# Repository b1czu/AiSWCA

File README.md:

# AiSWCA
AiSWCA is Steering Wheel Control Adapter

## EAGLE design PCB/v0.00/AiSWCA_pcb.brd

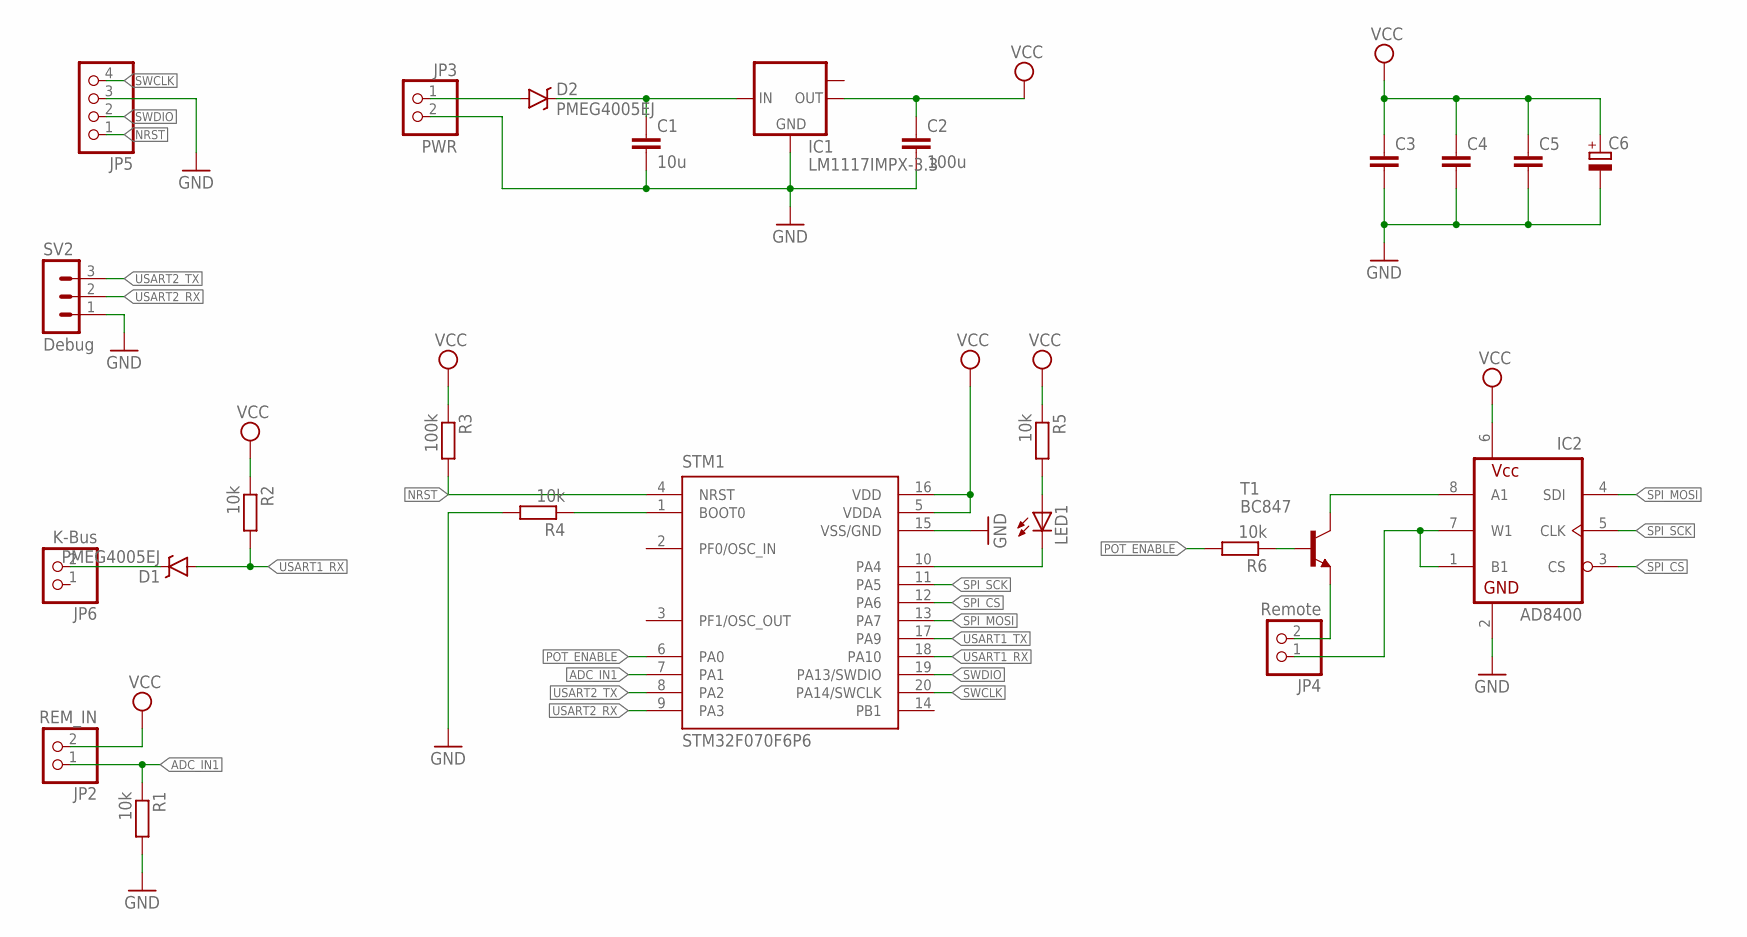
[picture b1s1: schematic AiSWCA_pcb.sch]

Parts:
C1: 10u; C0805
C2: 100u; C0805
C3, C4, C5: C-EUC0805; C0805
C6: CPOL-EUB/3528-21W; B/3528-21W
D1, D2: PMEG4005EJ; SOD-323
IC1: LM1117IMPX-3.3; SOT223
IC2: AD8400R; SO8
JP2: REM_IN; 1X02/90
JP3: PWR; 1X02/90
JP4: Remote; 1X02/90
JP5: PINHD-1X4/90; 1X04/90
JP6: K-Bus; 1X02/90
LED1: LEDCHIP-LED0805; CHIP-LED0805
R1, R2, R4, R5, R6: 10k; R0805
R3: 100k; R0805
STM1: STM32F070F6P6; TSSOP20
SV2: Debug; MA03-1
T1: BC847; SOT23

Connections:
ADC_IN1: JP2.1, R1.1, STM1.7 (PA1)
GND: C1.2, C2.2, C3.2, C4.2, C5.2, C6.-, IC1.1 (GND), IC2.2 (GND), JP3.2, JP5.3, R1.2, R4.2, STM1.15 (VSS/GND), SV2.1
unnamed: C1.1, D2.C, IC1.3 (IN)
unnamed: R4.1, STM1.1 (BOOT0)
unnamed: D1.C, JP6.2
unnamed: D2.A, JP3.1
unnamed: LED1.C, STM1.10 (PA4)
unnamed: LED1.A, R5.2
unnamed: JP4.2, T1.2 (E)
unnamed: IC2.8 (A1), T1.3 (C)
unnamed: IC2.1 (B1), IC2.7 (W1), JP4.1
unnamed: R6.1, T1.1 (B)
NRST: JP5.1, R3.2, STM1.4 (NRST)
POT_ENABLE: R6.2, STM1.6 (PA0)
SPI_CS: IC2.3 (CS), STM1.12 (PA6)
SPI_MOSI: IC2.4 (SDI), STM1.13 (PA7)
SPI_SCK: IC2.5 (CLK), STM1.11 (PA5)
SWCLK: JP5.4, STM1.20 (PA14/SWCLK)
SWDIO: JP5.2, STM1.19 (PA13/SWDIO)
USART1_RX: D1.A, R2.2, STM1.18 (PA10)
USART1_TX: STM1.17 (PA9)
USART2_RX: STM1.9 (PA3), SV2.2
USART2_TX: STM1.8 (PA2), SV2.3
VCC: C2.1, C3.1, C4.1, C5.1, C6.+, IC1.2 (OUT), IC2.6 (VDD), JP2.2, R2.1, R3.1, R5.1, STM1.5 (VDDA), STM1.16 (VDD)

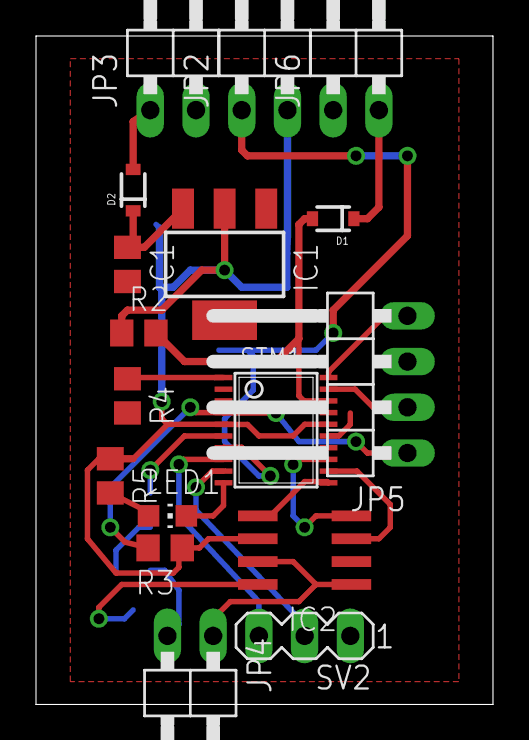
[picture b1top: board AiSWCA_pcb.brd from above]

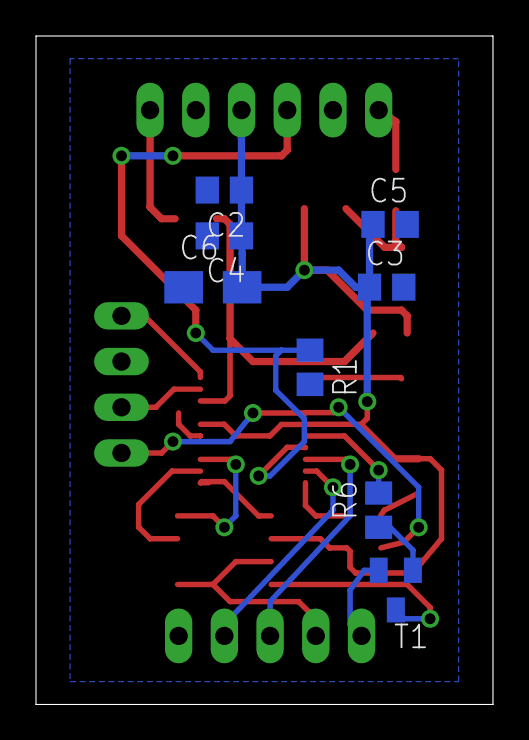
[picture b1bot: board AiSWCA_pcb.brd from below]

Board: 2 copper layers, 25.4 x 37.1 mm, 25 parts (8 on the bottom side), 23 nets.

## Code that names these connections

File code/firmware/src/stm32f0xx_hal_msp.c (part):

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    __HAL_RCC_ADC1_CLK_ENABLE();

    /**ADC GPIO Configuration
    PA1     ------> ADC_IN1
    */
    GPIO_InitStruct.Pin = GPIO_PIN_1;
    GPIO_InitStruct.Mode = GPIO_MODE_ANALOG;
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    __HAL_RCC_ADC1_CLK_DISABLE();

    /**ADC GPIO Configuration
    PA1     ------> ADC_IN1
    */
    HAL_GPIO_DeInit(GPIOA, GPIO_PIN_1);

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    __HAL_RCC_SPI1_CLK_ENABLE();

    /**SPI1 GPIO Configuration
    PA5     ------> SPI1_SCK
    PA7     ------> SPI1_MOSI
    */
    GPIO_InitStruct.Pin = GPIO_PIN_5|GPIO_PIN_7;
    GPIO_InitStruct.Mode = GPIO_MODE_AF_PP;
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    __HAL_RCC_SPI1_CLK_DISABLE();

    /**SPI1 GPIO Configuration
    PA5     ------> SPI1_SCK
    PA7     ------> SPI1_MOSI
    */
    HAL_GPIO_DeInit(GPIOA, GPIO_PIN_5|GPIO_PIN_7);

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
    /**USART1 GPIO Configuration
    PA9     ------> USART1_TX
    PA10     ------> USART1_RX
    */
    GPIO_InitStruct.Pin = GPIO_PIN_9|GPIO_PIN_10;
    GPIO_InitStruct.Mode = GPIO_MODE_AF_PP;
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    __HAL_RCC_USART2_CLK_ENABLE();

    /**USART2 GPIO Configuration
    PA2     ------> USART2_TX
    PA3     ------> USART2_RX
    */
    GPIO_InitStruct.Pin = GPIO_PIN_2|GPIO_PIN_3;
    GPIO_InitStruct.Mode = GPIO_MODE_AF_PP;
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
    /**USART1 GPIO Configuration
    PA9     ------> USART1_TX
    PA10     ------> USART1_RX
    */
    HAL_GPIO_DeInit(GPIOA, GPIO_PIN_9|GPIO_PIN_10);

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    __HAL_RCC_USART2_CLK_DISABLE();

    /**USART2 GPIO Configuration
    PA2     ------> USART2_TX
    PA3     ------> USART2_RX
    */
    HAL_GPIO_DeInit(GPIOA, GPIO_PIN_2|GPIO_PIN_3);

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
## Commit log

2016-06-25 Added first version of schematics and board layout.
2016-06-25 Cleanup in /PCB/
2016-06-25 Replaced previous Schottky diode with one in SOD323 package.
2016-07-03 Added static library stm32F0xx_HAL
2016-07-04 Added project template for AiSWCA (blinking led)
2016-07-04 .gitignore for c/cpp project
2016-07-05 Change the definition of processor(CPU_MODEL_GENERAL in lib/Makefile)
2016-07-16 Added error handler and system time.
2016-07-16 Added led driver.
2016-07-16 Added CLI file
2016-07-16 Added device_cfg.h and firmware_cfg.h
2016-07-16 Added AD8400 driver (dpot.h, dpot.c) + .gitignore
2016-07-16 Removed unused file
2016-07-16 Added k-bus driver
2016-07-16 Added Eclipse specific files to .gitignore
2016-07-16 Added extra #define to Makefile, cleanup.
2016-07-16 Added logger (cli.h)
2016-07-18 Added stm32f0xx_hal_msp.c file containing peripherial configuration
2016-07-18 Changed GPIOA speed to GPIO_SPEED_FREQ_HIGH
2016-07-18 Added digital pot driver. (UNTESTED!!!)
2016-07-18 Fixup! Added digital pot driver.
2016-07-18 Added first part of KBUS frame parser (CRC checker) Frame data is built in UART IRQ and checked against KBUS frame specs. Frame with bad LENGTH byte is dropped, frame with bad checksum is dropped.
2016-07-19 Fixup! Added first part of KBUS frame parser (CRC checker)
2016-07-19 Fixed off-by-one error.
2016-07-19 Added fifo (UNTESTED!!!)
2016-07-26 Added ADC
2016-07-31 Added analog watchdog out-of-window configuration.
2016-07-31 Improved ADC measurement. ADC is triggers by TIMER3. Timer frequence is 100 Hz (#define TIMER_FREQUENCY 100)
2016-07-31 Cleanup in ADC, added some comments.
2016-07-31 Added adc_logic function.
2016-09-15 Added radio config file (predefined resistance value)
2016-09-15 Added diode (SOD323 package) on power section
2016-10-10 Added values to some of elements on schematics.
2016-10-11 Fixed KBUS frame handler, changed KBUS UART configuration (BMW IBUS/KBUS uses 8 data bits, 1 stop bit, even parity, 9600 baud)
2016-10-12 Change Debug UART baudrate to 115200
2016-10-12 Changed KBUS USART error messages
2016-10-12 Added KBUS message definitions
2016-10-12 Changed includes to get rid of multiple inclusion Only put includes in a header if the header itself needs them. Examples: -Your function returns or takes as param type size_t. Then #include <stddef.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
2016-10-12 Fixed error in debug message
2016-10-12 Added KBUS parser test function, fixed errors in KBUS messages defs
2016-10-12 pseudo optimizations
2017-05-07 grudniowy sznurek (driving pot by kbus by easiest possible way)
2017-05-07 Resolved "hanging fastforward bug"

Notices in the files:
code/firmware/src/stm32f0xx_hal_msp.c:
COPYRIGHT(c) 2016 STMicroelectronics
(C) COPYRIGHT STMicroelectronics *****END OF FILE
parts and their libraries:
SparkFun-DiscreteSemi: Licensing: Creative Commons ShareAlike 4.0 International - https://creativecommons.org/licenses/by-sa/4.0
